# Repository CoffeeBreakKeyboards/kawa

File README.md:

# Kawa
## a 32 key 'fixed-split' keyboard
This is currently a work in progress. I am currently learning PCB design for 
keyboards and this will be my first project. 
Readme updates will follow further builds.

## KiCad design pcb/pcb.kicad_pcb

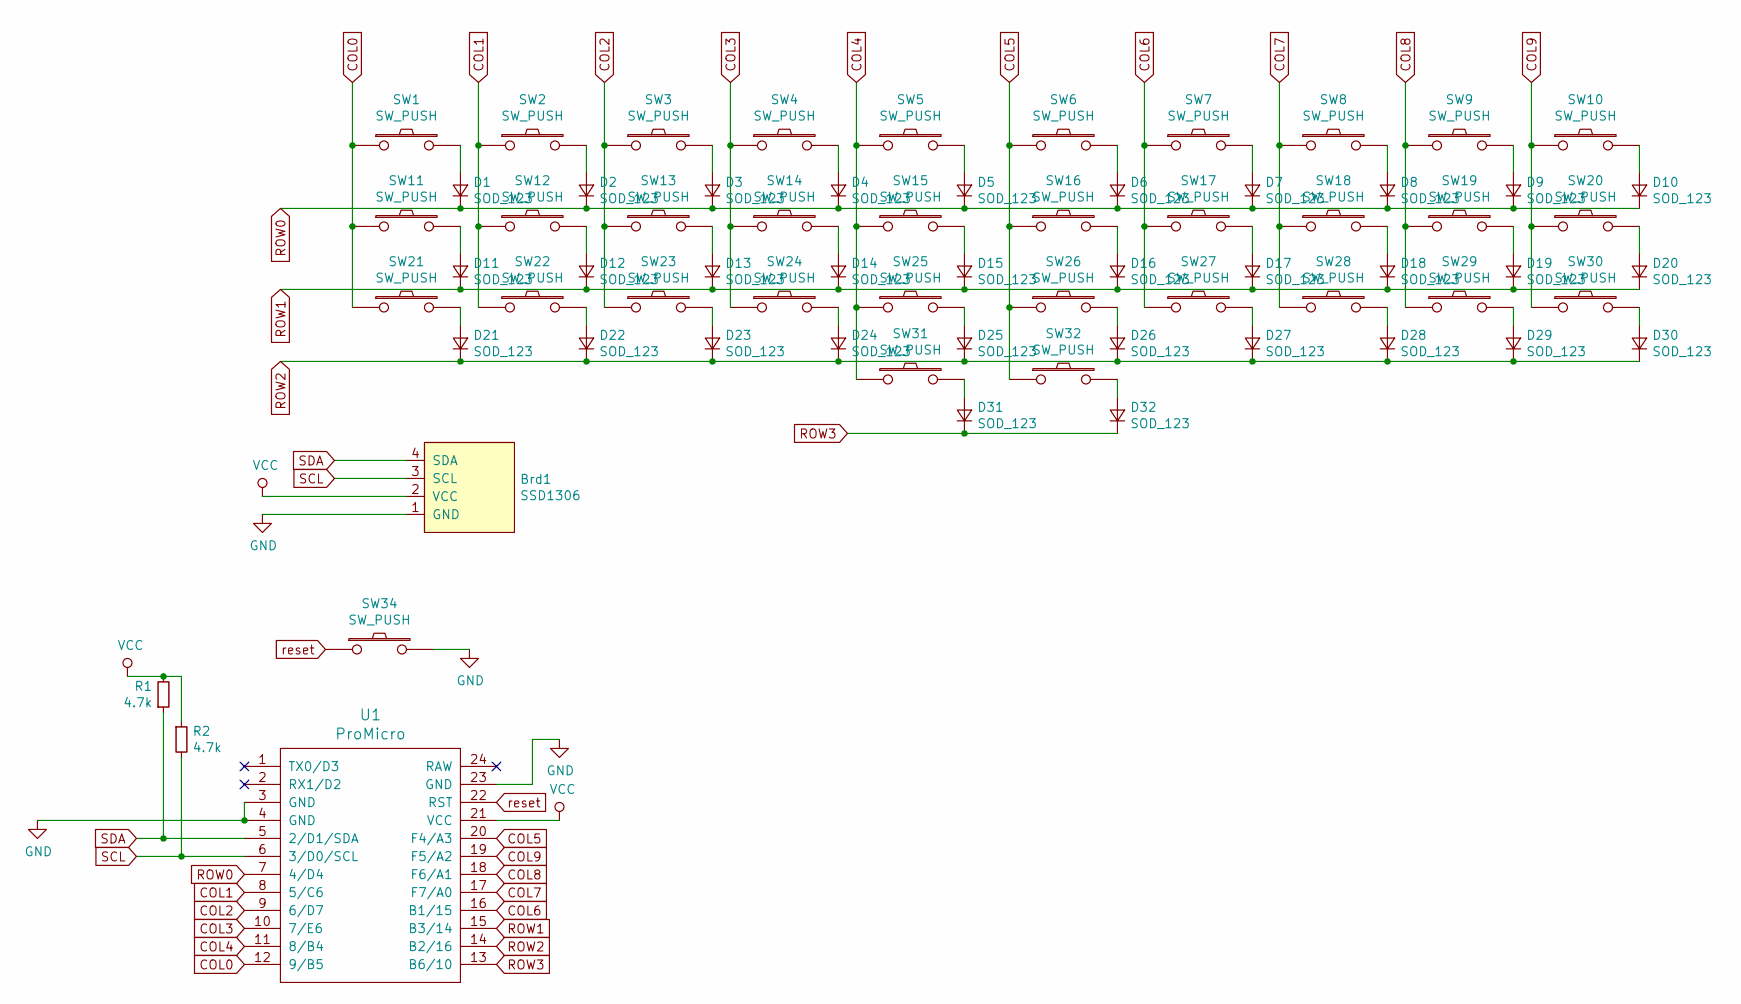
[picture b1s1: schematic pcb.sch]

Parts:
Brd1: SSD1306; 128x64OLED
D1, D2, D3, D4, D5, D6, D7, D8, D9, D10, D11, D12, D13, D14, D15, D16, D17, D18, D19, D20, D21, D22, D23, D24, D25, D26, D27, D28, D29, D30, D31, D32: SOD_123; D3_TH
R1, R2: 4.7k; R_Axial_DIN0204_L3.6mm_D1.6mm_P1.90mm_Vertical
SW1, SW2, SW3, SW4, SW5, SW6, SW7, SW8, SW9, SW10, SW11, SW12, SW13, SW14, SW15, SW16, SW17, SW18, SW19, SW20, SW21, SW22, SW23, SW24, SW25, SW26, SW27, SW28, SW29, SW30: SW_PUSH; MXOnly-1U-NoLED
SW31, SW32: SW_PUSH; MXOnly-2U-NoLED
SW34: SW_PUSH; ResetSW_1side
U1: ProMicro; ProMicro_v3.5

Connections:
COL0: SW1.1, SW11.1, SW21.1, U1.12 (9/B5)
COL1: SW2.1, SW12.1, SW22.1, U1.8 (5/C6)
COL2: SW3.1, SW13.1, SW23.1, U1.9 (6/D7)
COL3: SW4.1, SW14.1, SW24.1, U1.10 (7/E6)
COL4: SW5.1, SW15.1, SW25.1, SW31.1, U1.11 (8/B4)
COL5: SW6.1, SW16.1, SW26.1, SW32.1, U1.20 (F4/A3)
COL6: SW7.1, SW17.1, SW27.1, U1.16 (B1/15)
COL7: SW8.1, SW18.1, SW28.1, U1.17 (F7/A0)
COL8: SW9.1, SW19.1, SW29.1, U1.18 (F6/A1)
COL9: SW10.1, SW20.1, SW30.1, U1.19 (F5/A2)
GND: Brd1.1 (GND), SW34.2, U1.3 (GND), U1.4 (GND), U1.23 (GND)
unnamed: D1.2 (A), SW1.2
unnamed: D2.2 (A), SW2.2
unnamed: D3.2 (A), SW3.2
unnamed: D4.2 (A), SW4.2
unnamed: D5.2 (A), SW5.2
unnamed: D6.2 (A), SW6.2
unnamed: D7.2 (A), SW7.2
unnamed: D8.2 (A), SW8.2
unnamed: D9.2 (A), SW9.2
unnamed: D10.2 (A), SW10.2
unnamed: D11.2 (A), SW11.2
unnamed: D12.2 (A), SW12.2
unnamed: D13.2 (A), SW13.2
unnamed: D14.2 (A), SW14.2
unnamed: D15.2 (A), SW15.2
unnamed: D16.2 (A), SW16.2
unnamed: D17.2 (A), SW17.2
unnamed: D18.2 (A), SW18.2
unnamed: D19.2 (A), SW19.2
unnamed: D20.2 (A), SW20.2
unnamed: D21.2 (A), SW21.2
unnamed: D22.2 (A), SW22.2
unnamed: D23.2 (A), SW23.2
unnamed: D24.2 (A), SW24.2
unnamed: D25.2 (A), SW25.2
unnamed: D26.2 (A), SW26.2
unnamed: D27.2 (A), SW27.2
unnamed: D28.2 (A), SW28.2
unnamed: D29.2 (A), SW29.2
unnamed: D30.2 (A), SW30.2
unnamed: D31.2 (A), SW31.2
unnamed: D32.2 (A), SW32.2
ROW0: D1.1 (K), D2.1 (K), D3.1 (K), D4.1 (K), D5.1 (K), D6.1 (K), D7.1 (K), D8.1 (K), D9.1 (K), D10.1 (K), U1.7 (4/D4)
ROW1: D11.1 (K), D12.1 (K), D13.1 (K), D14.1 (K), D15.1 (K), D16.1 (K), D17.1 (K), D18.1 (K), D19.1 (K), D20.1 (K), U1.15 (B3/14)
ROW2: D21.1 (K), D22.1 (K), D23.1 (K), D24.1 (K), D25.1 (K), D26.1 (K), D27.1 (K), D28.1 (K), D29.1 (K), D30.1 (K), U1.14 (B2/16)
ROW3: D31.1 (K), D32.1 (K), U1.13 (B6/10)
SCL: Brd1.3 (SCL), R2.2, U1.6 (3/D0/SCL)
SDA: Brd1.4 (SDA), R1.1, U1.5 (2/D1/SDA)
VCC: Brd1.2 (VCC), R1.2, R2.1, U1.21 (VCC)
reset: SW34.1, U1.22 (RST)

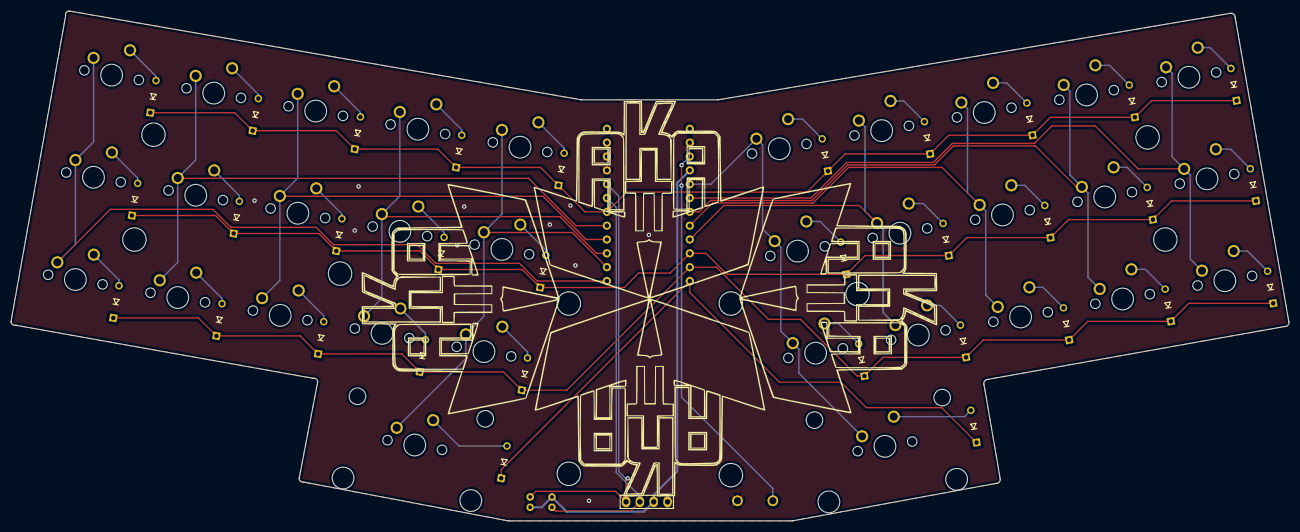
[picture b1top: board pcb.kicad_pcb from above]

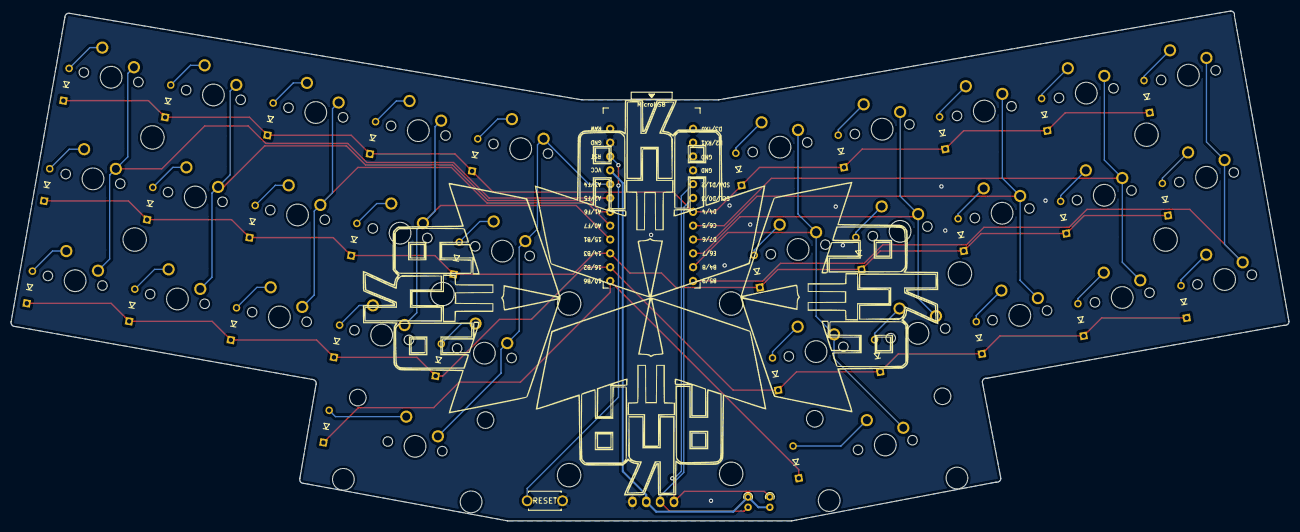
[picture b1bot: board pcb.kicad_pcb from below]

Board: 2 copper layers, 234.6 x 93.6 mm, 79 parts (36 on the bottom side), 51 nets.

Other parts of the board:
Ref**: Val**; M2_HOLE_v2
Ref**#2, Ref**#3, Ref**#4, Ref**#5, Ref**#6, Ref**#7, Ref**#8, Ref**#9, Ref**#10: Val**; M2_HOLE_v2

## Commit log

2020-08-16 Adds readme
2020-08-16 Adds foostan/kbd submodule, adds pcb project folder
2020-08-16 Adds type-c ai03 library, continues work on schematic
2020-08-16 Completes schematic, adds more submodules
2020-08-16 Moves some submodules around, completes placement of components.
2020-08-17 Continues working on routing, moved to using some different components
2020-08-17 Fixes submodules
2020-08-17 Fixing submodules more
2020-08-18 Finishes routing
2020-08-18 Adds groundfill, gerbers
2020-08-18 Moves gerbers, adds gerbers zip
2020-08-18 Fixes edgecut, updates gerbers and zip
2020-08-18 Updates to fill and slight update to routing for a nicer look
2020-08-18 Fully reroutes and updates schematic, fixes issues with columns, adds I2C pull up resistors, adds beginning of bottom plate
2020-09-05 Major updates
2020-09-12 Finishes transition to arm / usb c
2020-10-25 Finishes reroute
2020-10-25 Updates gerber.zip
2020-11-02 Finishes move back to pro micro, adds silk footprint and lib, updates routing, fixes outline
2020-11-02 Adds m2 holes, adds updated gerbers
2020-11-02 Updates gerbers.zip
2020-11-04 Updates for silk
2020-11-07 Updates kawa to remove encoder, adds new oled footprint, reroute accordingly
2020-11-10 Updates kawa gerbers with m2 holes
